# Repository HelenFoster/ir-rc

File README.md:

Infrared remote control experiments
=====

The aim is to have a tiny transmitter which works with the OpenPandora without compromising on its handheld quality. (For receivers, this is not a problem, because they are generally resting on a solid surface while you send them signals from somewhere else. But for a transmitter, handheld is very useful!)

Currently using very simple descriptions of the waveforms (and two different waveforms per code for the protocols with a toggle bit). Later it would be useful to handle the actual protocols, e.g. integrate with LIRC.

Licensing
----
C code: MIT License (see code headers)
Schematic and PCB files: CC BY-SA http://creativecommons.org/licenses/by-sa/4.0/

rx_dur (Arduino)
----
Monitors a digital signal on the specified pin, waits for this signal to match the trigger level, and outputs a list of comma-separate durations (in microseconds) on Serial. The first duration is the length of time the signal stays at the trigger level; the second is the length of time it stays at the opposite level after that; and so on. It records data until the buffer is full or until the specified maximum time after the trigger, then it transmits on Serial afterwards.

This can be connected to an IR demodulator device to read remote control signals.

tx_tone (Arduino)
----
Reads a comma-separated list of durations (in microseconds) from Serial, and outputs the 38kHz modulated version on the specified pin, using the Arduino tone function. The first duration is the length of the first burst; the second duration is the length of the first space; and so on. The bursts seem to come out about 40us shorter than specified (and the spaces about 40us longer), but the devices I have tested are not fussy about this.

From a handheld perspective, the Uno is too big, and the Nano does not seem to work on the Pandora without a hub.

circuits/led_driver_5V
----
This circuit drives the LED with about 150mA while only drawing a maximum of 23mA from the power supply. It is useful for USB-connected devices like Arduino, on the Pandora's OTG port which can only provide 100mA. The signal output pin from the Arduino is connected to the gate of the MOSFET (signal is active high).

circuits/ftdi_pic_ir
----
This circuit connects an 8-pin PIC with the LED driver and an FTDI Basic Breakout board. (The FT232R bitbang mode looked promising for making the remote control signals itself, but seems to be not sufficiently accurate. So this design uses serial mode with a PIC instead.) The PCB is not tested yet!

tx_pic (PIC12F683)
----
This uses duration-based serial messages like the Arduino projects, but using binary data instead of text to save RAM. The first byte is the carrier period (usually 26); the second byte is a multiplier for burst durations; and the remaining bytes are for the durations not yet multiplied, on-off-on-off-etc (all times in microseconds). The program echoes the serial data received, plus an "ok" or error string.

The buffer is currently 80 bytes long, which is enough for most things. Clearing more space for it would probably involve making the code less readable.

The UART timing is somewhat relying on the time taken by instructions, and might be wrong with a different compiler or compiler settings. I wrote that part first on a less capable PIC. It would be better to use Timer2 instead of Timer0 (and abstract out the delay using the wait_T2 function which is already there).

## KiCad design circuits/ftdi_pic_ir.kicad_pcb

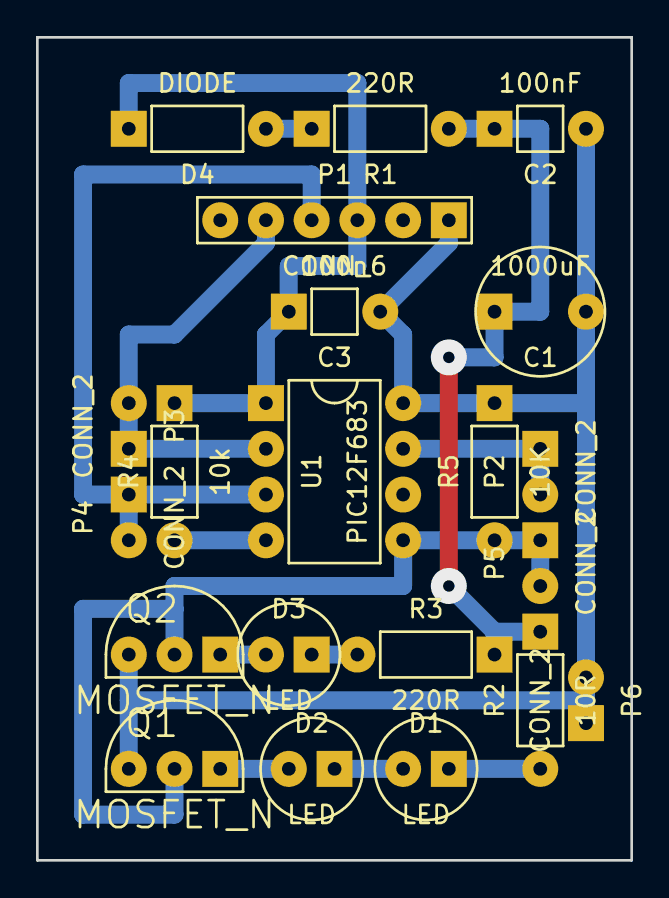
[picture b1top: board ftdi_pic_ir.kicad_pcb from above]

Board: 2 copper layers, 33.0 x 45.7 mm, 21 parts (0 on the bottom side), 14 nets.

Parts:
C1: 1000uF; CHUNKY_RADIAL-3
C2: 100nF; CHUNKY_AXIAL-3
C3: 100n; CHUNKY_AXIAL-3
D1, D2, D3: LED; CHUNKY_RADIAL-2
D4: DIODE; CHUNKY_AXIAL-4
P1: CONN_6; CHUNKY_SIL-6
P2, P3, P4, P5, P6: CONN_2; CHUNKY_AXIAL-2
Q1, Q2: MOSFET_N; CHUNKY_2N7000
R1, R3: 220R; CHUNKY_AXIAL-4
R2: 10R; CHUNKY_AXIAL-4
R4: 10k; CHUNKY_AXIAL-4
R5: 10K; CHUNKY_AXIAL-4
U1: PIC12F683; CHUNKY_DIP-8

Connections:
5V: C3.1, D4.1, P1.3, R4.1, U1.1
FTDI_RX__PIC_TX: P1.5, P3.1, P3.2, U1.2
FTDI_TX__PIC_RX: P1.4, P4.1, P4.2, U1.3
GND: C1.2, C2.2, C3.2, P1.1, P6.1, P6.2, Q1.S, Q2.S, R5.1, U1.8
unnamed: D3.1, R3.2
unnamed: P2.1, P2.2, U1.7
unnamed: D3.2, Q2.D
unnamed: D1.1, R2.2
unnamed: D1.2, D2.1
unnamed: D4.2, R1.1
unnamed: R4.2, U1.4
unnamed: D2.2, Q1.D
unnamed: C1.1, C2.1, R1.2, R2.1, R3.1
signal: P5.1, P5.2, Q1.G, Q2.G, R5.2, U1.5

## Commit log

2014-05-30 Start readme.
2014-05-31 Added previous Arduino projects.
2014-05-31 Added LED circuit
2014-06-06 Modified LED driver circuit
2014-06-06 Working on PCB for PIC circuit
2014-06-08 Added ground clip to PIC circuit
2014-06-08 Moved a track on PIC circuit
2014-06-08 Added PIC program
2015-11-20 Arduino receiver: reduced precision to store more values
2016-01-17 Arduino transmitter: real PWM option, so we can vary the duty cycle
